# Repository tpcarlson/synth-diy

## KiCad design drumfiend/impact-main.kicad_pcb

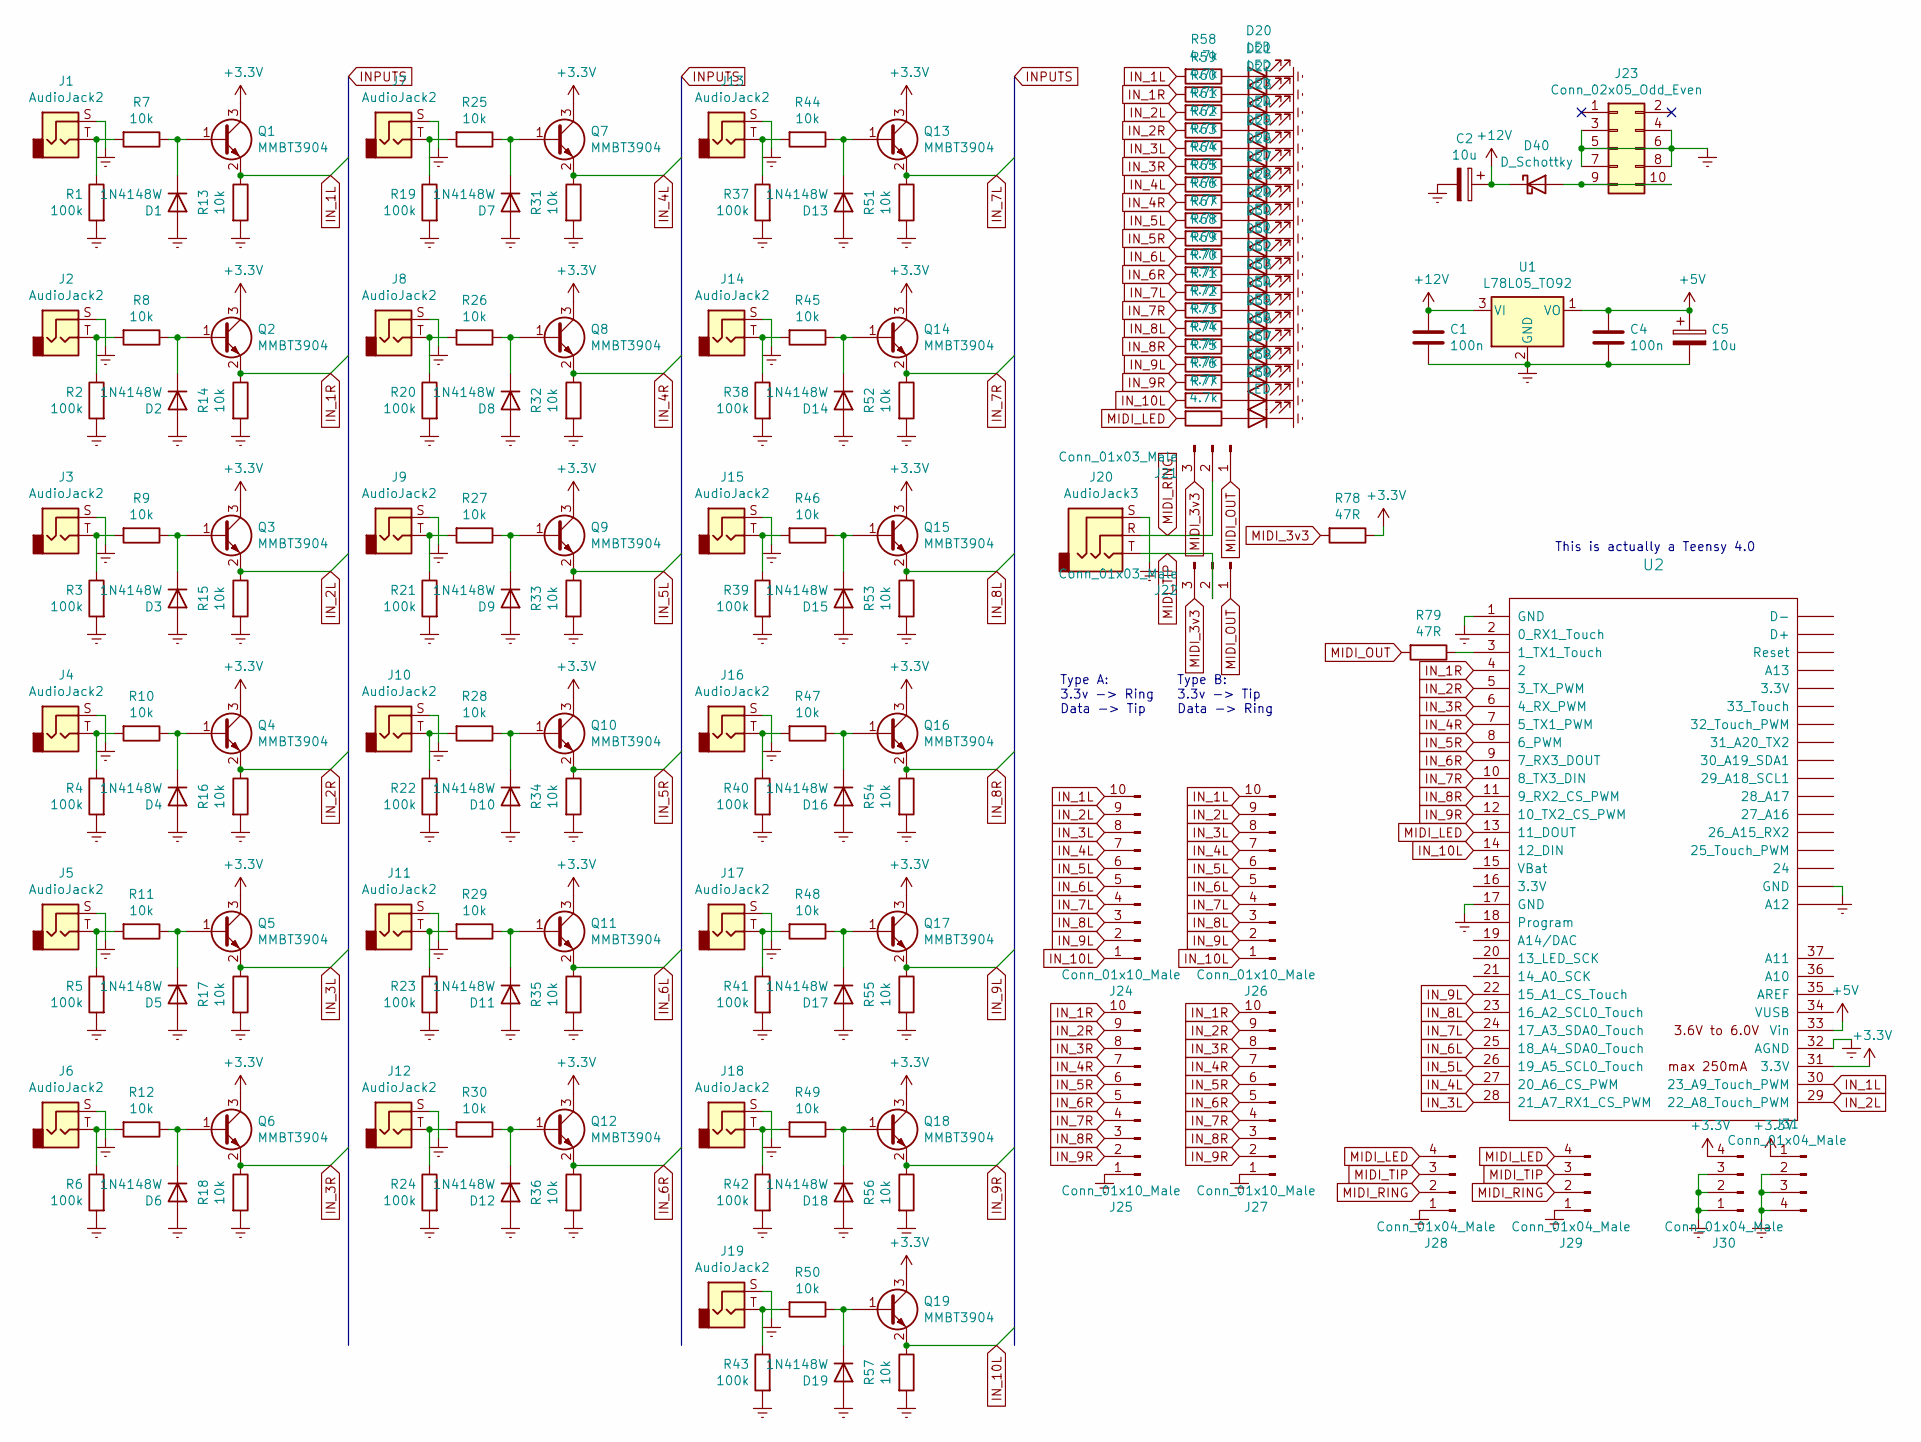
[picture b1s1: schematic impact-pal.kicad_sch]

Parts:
C1, C4: 100n; C_Disc_D5.0mm_W2.5mm_P2.50mm
C2, C5: 10u; CP_Radial_D5.0mm_P2.50mm
D1, D2, D3, D4, D5, D6, D7, D8, D9, D10, D11, D12, D13, D14, D15, D16, D17, D18, D19: 1N4148W; D_SOD-123
D20, D21, D22, D23, D24, D25, D26, D27, D28, D29, D30, D31, D32, D33, D34, D35, D36, D37, D38, D39: LED; LED_D3.0mm
D40: D_Schottky; D_A-405_P7.62mm_Horizontal
J1, J2, J3, J4, J5, J6, J7, J8, J9, J10, J11, J12, J13, J14, J15, J16, J17, J18, J19: AudioJack2; Jack_3.5mm_QingPu_WQP-PJ398SM_Vertical_CircularHoles
J20: AudioJack3; Jack_3.5mm_QingPu_WQP-PJ398SM_Vertical_CircularHoles
J21, J22: Conn_01x03_Male; PinHeader_1x03_P2.54mm_Vertical
J23: Conn_02x05_Odd_Even; IDC-Header_2x05_P2.54mm_Vertical
J24, J25, J26, J27: Conn_01x10_Male; PinHeader_1x10_P2.54mm_Vertical
J28, J29, J30, J31: Conn_01x04_Male; PinHeader_1x04_P2.54mm_Vertical
Q1, Q2, Q3, Q4, Q5, Q6, Q7, Q8, Q9, Q10, Q11, Q12, Q13, Q14, Q15, Q16, Q17, Q18, Q19: MMBT3904; SOT-23
R1, R2, R3, R4, R5, R6, R19, R20, R21, R22, R23, R24, R37, R38, R39, R40, R41, R42, R43: 100k; R_0805_2012Metric
R7, R8, R9, R10, R11, R12, R13, R14, R15, R16, R17, R18, R25, R26, R27, R28, R29, R30, R31, R32, R33, R34, R35, R36, R44, R45, R46, R47, R48, R49, R50, R51, R52, R53, R54, R55, R56, R57: 10k; R_0805_2012Metric
R58, R59, R60, R61, R62, R63, R64, R65, R66, R67, R68, R69, R70, R71, R72, R73, R74, R75, R76, R77: 4.7k; R_0805_2012Metric
R78, R79: 47R; R_Axial_DIN0207_L6.3mm_D2.5mm_P7.62mm_Horizontal
U1: L78L05_TO92; TO-92_Inline_Wide
U2: (no value)

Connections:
+3V3: J30.4, J31.1, Q1.3 (C), Q2.3 (C), Q3.3 (C), Q4.3 (C), Q5.3 (C), Q6.3 (C), Q7.3 (C), Q8.3 (C), Q9.3 (C), Q10.3 (C), Q11.3 (C), Q12.3 (C), Q13.3 (C), Q14.3 (C), Q15.3 (C), Q16.3 (C), Q17.3 (C), Q18.3 (C), Q19.3 (C), R78.1, U2.31 (3.3V)
Earth: C1.2, C2.2, C4.2, C5.2, D1.2 (A), D2.2 (A), D3.2 (A), D4.2 (A), D5.2 (A), D6.2 (A), D7.2 (A), D8.2 (A), D9.2 (A), D10.2 (A), D11.2 (A), D12.2 (A), D13.2 (A), D14.2 (A), D15.2 (A), D16.2 (A), D17.2 (A), D18.2 (A), D19.2 (A), D20.1 (K), D21.1 (K), D22.1 (K), D23.1 (K), D24.1 (K), D25.1 (K), D26.1 (K), D27.1 (K), D28.1 (K), D29.1 (K), D30.1 (K), D31.1 (K), D32.1 (K), D33.1 (K), D34.1 (K), D35.1 (K), D36.1 (K), D37.1 (K), D38.1 (K), D39.1 (K), J1.S, J2.S, J3.S, J4.S, J5.S, J6.S, J7.S, J8.S, J9.S, J10.S, J11.S, J12.S, J13.S, J14.S, J15.S, J16.S, J17.S, J18.S, J19.S, J20.S, J23.3, J23.4, J23.5, J23.6, J23.7, J23.8, J25.1, J27.1, J28.1, J29.1, J30.1, J30.2, J30.3, J31.2, J31.3, J31.4, R1.2, R2.2, R3.2, R4.2, R5.2, R6.2, R13.2, R14.2, R15.2, R16.2, R17.2, R18.2, R19.2, R20.2, R21.2, R22.2, R23.2, R24.2, R31.2, R32.2, R33.2, R34.2, R35.2, R36.2, R37.2, R38.2, R39.2, R40.2, R41.2, R42.2, R43.2, R51.2, R52.2, R53.2, R54.2, R55.2, R56.2, R57.2, U1.2 (GND), U2.1 (GND), U2.17 (GND), U2.32 (AGND), U2.~ (24)
IN_1L: J24.10, J26.10, Q1.2 (E), R13.1, R58.2, U2.30 (23_A9_Touch_PWM)
IN_1R: J25.10, J27.10, Q2.2 (E), R14.1, R59.2, U2.4 (2)
IN_2L: J24.9, J26.9, Q3.2 (E), R15.1, R60.2, U2.29 (22_A8_Touch_PWM)
IN_2R: J25.9, J27.9, Q4.2 (E), R16.1, R61.2, U2.5 (3_TX_PWM)
IN_3L: J24.8, J26.8, Q5.2 (E), R17.1, R62.2, U2.28 (21_A7_RX1_CS_PWM)
IN_3R: J25.8, J27.8, Q6.2 (E), R18.1, R63.2, U2.6 (4_RX_PWM)
IN_4L: J24.7, J26.7, Q7.2 (E), R31.1, R64.2, U2.27 (20_A6_CS_PWM)
IN_4R: J25.7, J27.7, Q8.2 (E), R32.1, R65.2, U2.7 (5_TX1_PWM)
IN_5L: J24.6, J26.6, Q9.2 (E), R33.1, R66.2, U2.26 (19_A5_SCL0_Touch)
IN_5R: J25.6, J27.6, Q10.2 (E), R34.1, R67.2, U2.8 (6_PWM)
IN_6L: J24.5, J26.5, Q11.2 (E), R35.1, R68.2, U2.25 (18_A4_SDA0_Touch)
IN_6R: J25.5, J27.5, Q12.2 (E), R36.1, R69.2, U2.9 (7_RX3_DOUT)
IN_7L: J24.4, J26.4, Q13.2 (E), R51.1, R70.2, U2.24 (17_A3_SDA0_Touch)
IN_7R: J25.4, J27.4, Q14.2 (E), R52.1, R71.2, U2.10 (8_TX3_DIN)
IN_8L: J24.3, J26.3, Q15.2 (E), R53.1, R72.2, U2.23 (16_A2_SCL0_Touch)
IN_8R: J25.3, J27.3, Q16.2 (E), R54.1, R73.2, U2.11 (9_RX2_CS_PWM)
IN_9L: J24.2, J26.2, Q17.2 (E), R55.1, R74.2, U2.22 (15_A1_CS_Touch)
IN_9R: J25.2, J27.2, Q18.2 (E), R56.1, R75.2, U2.12 (10_TX2_CS_PWM)
IN_10L: J24.1, J26.1, Q19.2 (E), R57.1, R76.2, U2.14 (12_DIN)
MIDI_LED: J28.4, J29.4, R77.2, U2.13 (11_DOUT)
MIDI_RING: J20.R, J21.2, J28.2, J29.2
MIDI_TIP: J20.T, J22.2, J28.3, J29.3
unnamed: C1.1, C2.1, D40.1 (K), U1.3 (VI)
unnamed: C4.1, C5.1, U1.1 (VO), U2.33 (Vin)
unnamed: D1.1 (K), Q1.1 (B), R7.1
unnamed: D2.1 (K), Q2.1 (B), R8.1
unnamed: D3.1 (K), Q3.1 (B), R9.1
unnamed: D4.1 (K), Q4.1 (B), R10.1
unnamed: D5.1 (K), Q5.1 (B), R11.1
unnamed: D6.1 (K), Q6.1 (B), R12.1
unnamed: D7.1 (K), Q7.1 (B), R25.1
unnamed: D8.1 (K), Q8.1 (B), R26.1
unnamed: D9.1 (K), Q9.1 (B), R27.1
unnamed: D10.1 (K), Q10.1 (B), R28.1
unnamed: D11.1 (K), Q11.1 (B), R29.1
unnamed: D12.1 (K), Q12.1 (B), R30.1
unnamed: D13.1 (K), Q13.1 (B), R44.1
unnamed: D14.1 (K), Q14.1 (B), R45.1
unnamed: D15.1 (K), Q15.1 (B), R46.1
unnamed: D16.1 (K), Q16.1 (B), R47.1
unnamed: D17.1 (K), Q17.1 (B), R48.1
unnamed: D18.1 (K), Q18.1 (B), R49.1
unnamed: D19.1 (K), Q19.1 (B), R50.1
unnamed: D20.2 (A), R58.1
unnamed: D21.2 (A), R59.1
unnamed: D22.2 (A), R60.1
unnamed: D23.2 (A), R61.1
unnamed: D24.2 (A), R62.1
unnamed: D25.2 (A), R63.1
unnamed: D26.2 (A), R64.1
unnamed: D27.2 (A), R65.1
unnamed: D28.2 (A), R66.1
unnamed: D29.2 (A), R67.1
unnamed: D30.2 (A), R68.1
unnamed: D31.2 (A), R69.1
unnamed: D32.2 (A), R70.1
unnamed: D33.2 (A), R71.1
unnamed: D34.2 (A), R72.1
unnamed: D35.2 (A), R73.1
unnamed: D36.2 (A), R74.1
unnamed: D37.2 (A), R75.1
unnamed: D38.2 (A), R76.1
unnamed: D39.2 (A), R77.1
unnamed: D40.2 (A), J23.9, J23.10
unnamed: J1.T, R1.1, R7.2
unnamed: J2.T, R2.1, R8.2
unnamed: J3.T, R3.1, R9.2
unnamed: J4.T, R4.1, R10.2
unnamed: J5.T, R5.1, R11.2
unnamed: J6.T, R6.1, R12.2
unnamed: J7.T, R19.1, R25.2
unnamed: J8.T, R20.1, R26.2
unnamed: J9.T, R21.1, R27.2
unnamed: J10.T, R22.1, R28.2
unnamed: J11.T, R23.1, R29.2
unnamed: J12.T, R24.1, R30.2
unnamed: J13.T, R37.1, R44.2
unnamed: J14.T, R38.1, R45.2
unnamed: J15.T, R39.1, R46.2
unnamed: J16.T, R40.1, R47.2
unnamed: J17.T, R41.1, R48.2
unnamed: J18.T, R42.1, R49.2
unnamed: J19.T, R43.1, R50.2
unnamed: J21.1, J22.1, R79.2
unnamed: J21.3, J22.3, R78.2
unnamed: R79.1, U2.3 (1_TX1_Touch)

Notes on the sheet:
Type B: 3.3v -> Tip Data -> Ring
Type A: 3.3v -> Ring Data -> Tip
This is actually a Teensy 4.0

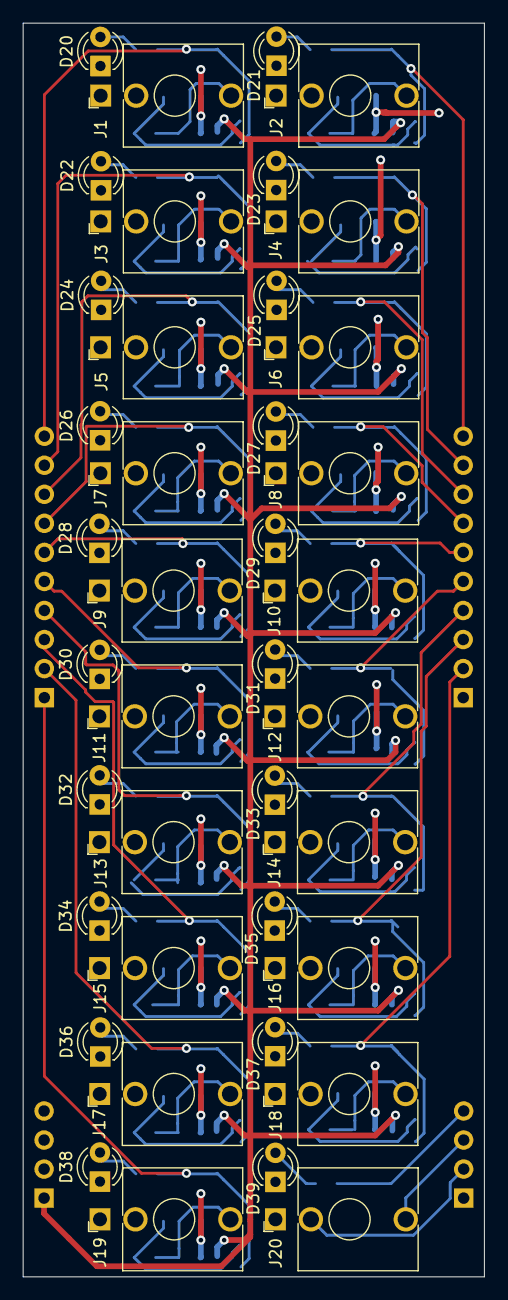
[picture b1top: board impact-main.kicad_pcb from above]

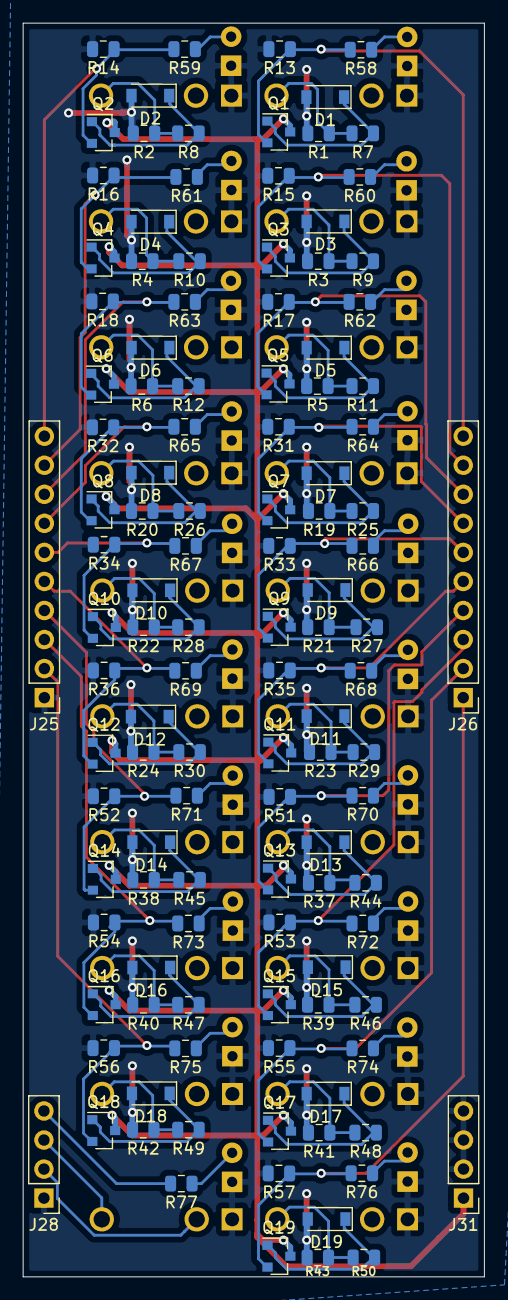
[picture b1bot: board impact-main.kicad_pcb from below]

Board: 2 copper layers, 40.3 x 109.6 mm, 159 parts (119 on the bottom side), 82 nets.

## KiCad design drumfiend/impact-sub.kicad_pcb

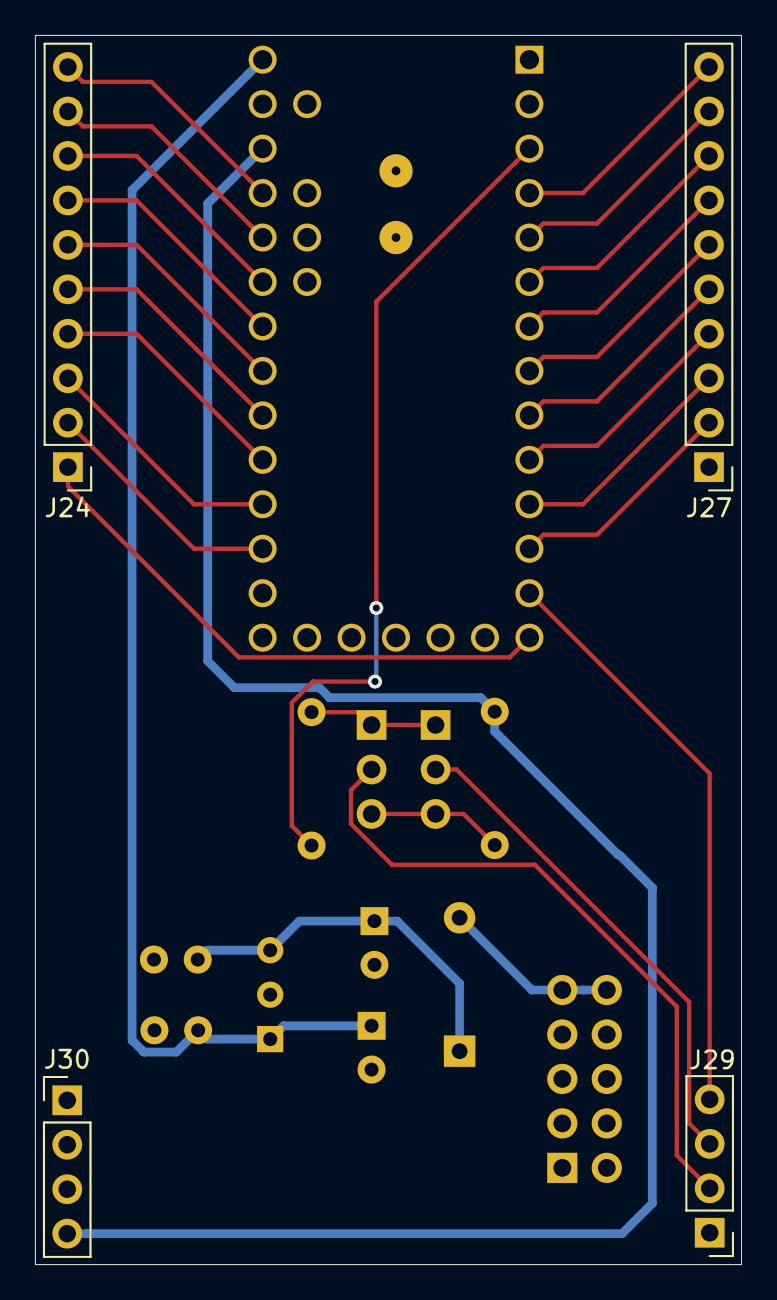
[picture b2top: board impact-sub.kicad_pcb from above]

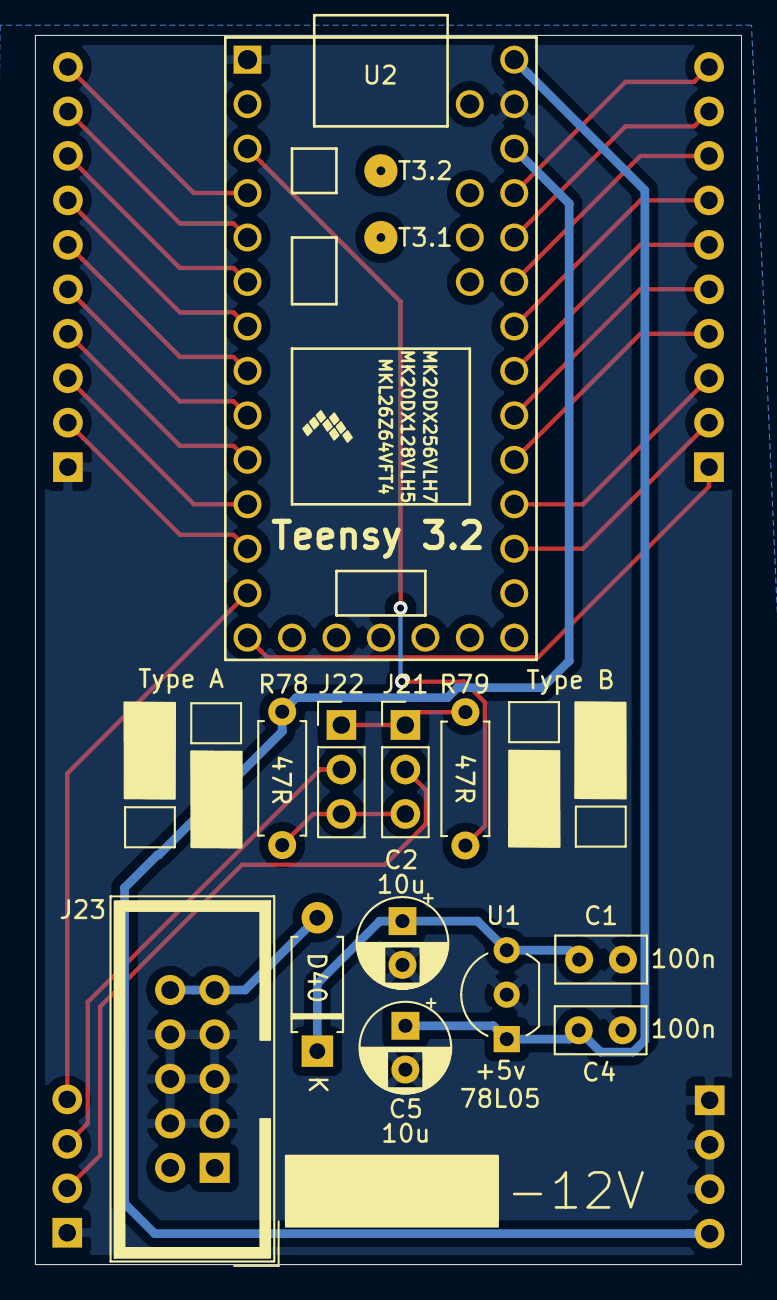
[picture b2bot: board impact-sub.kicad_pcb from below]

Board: 2 copper layers, 40.3 x 70.2 mm, 16 parts (12 on the bottom side), 30 nets.

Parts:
C1, C4: 100n; C_Disc_D5.0mm_W2.5mm_P2.50mm
C2, C5: 10u; CP_Radial_D5.0mm_P2.50mm
D40: D_Schottky; D_A-405_P7.62mm_Horizontal
J21, J22: Conn_01x03_Male; PinHeader_1x03_P2.54mm_Vertical
J23: Conn_02x05_Odd_Even; IDC-Header_2x05_P2.54mm_Vertical
J24, J27: Conn_01x10_Male; PinHeader_1x10_P2.54mm_Vertical
J29, J30: Conn_01x04_Male; PinHeader_1x04_P2.54mm_Vertical
R78, R79: 47R; R_Axial_DIN0207_L6.3mm_D2.5mm_P7.62mm_Horizontal
U1: L78L05_TO92; TO-92_Inline_Wide
U2: Teensy3.2; Teensy30_31_32_LC

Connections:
+3V3: J30.4, R78.1, U2.31
+5V: C4.1, C5.1, U1.1, U2.33
+12V: C1.1, C2.1, D40.1, U1.3
Earth: C1.2, C2.2, C4.2, C5.2, J23.3, J23.4, J23.5, J23.6, J23.7, J23.8, J27.1, J29.1, J30.1, J30.2, J30.3, U1.2, U2.1, U2.17, U2.32
IN_1L: J24.10, U2.30
IN_1R: J27.10, U2.4
IN_2L: J24.9, U2.29
IN_2R: J27.9, U2.5
IN_3L: J24.8, U2.28
IN_3R: J27.8, U2.6
IN_4L: J24.7, U2.27
IN_4R: J27.7, U2.7
IN_5L: J24.6, U2.26
IN_5R: J27.6, U2.8
IN_6L: J24.5, U2.25
IN_6R: J27.5, U2.9
IN_7L: J24.4, U2.24
IN_7R: J27.4, U2.10
IN_8L: J24.3, U2.23
IN_8R: J27.3, U2.11
IN_9L: J24.2, U2.22
IN_9R: J27.2, U2.12
IN_10L: J24.1, U2.14
MIDI_3v3: J21.3, J22.3, R78.2
MIDI_LED: J29.4, U2.13
MIDI_OUT: J21.1, J22.1, R79.2
MIDI_RING: J21.2, J29.2
MIDI_TIP: J22.2, J29.3
unnamed: D40.2, J23.9, J23.10
unnamed: R79.1, U2.3

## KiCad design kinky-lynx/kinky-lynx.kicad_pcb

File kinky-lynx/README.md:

# Kinky Lynx

##### What is this?

A mashup of Mutable Instruments' [Kinks](https://mutable-instruments.net/modules/kinks/) and [Links](https://mutable-instruments.net/modules/links/) all on one board.

##### How much power does it use?

(TBC) As measured by the joranalogue Test 3, around x mA on +12v and y mA on -12v at peak. The 5v rail is unused.

##### Where does the design come from?

This is just a copy of the Kinks and Links schematics jammed together on one PCB, with a couple of very small component changes to allow for easier assembly.

##### Are there any rare/weird parts used?

All fairly common parts. Some of the capacitors are quite small (0402 sized) which will make hand soldering a challenge, I had my boards assembled by the PCB fab. I used two pin bicolour LEDs, but you can substitute them for a normal 3mm LED.

##### Are there any problems with the design?

The topmost row (One in three out) seems to pull the LED to a negative voltage when nothing is plugged in, but other than everything works well!

##### Do you have a BOM/Mouser cart/Tayda links?

Sorry, no. Things go out of stock so frequently it'd be a lot of work to keep these up to date. Everything in this project is easy to source though, so you should not have any trouble.

##### Can I buy PCBs or a kit?

Send me an email (twigathy+synth@gmail.com)...

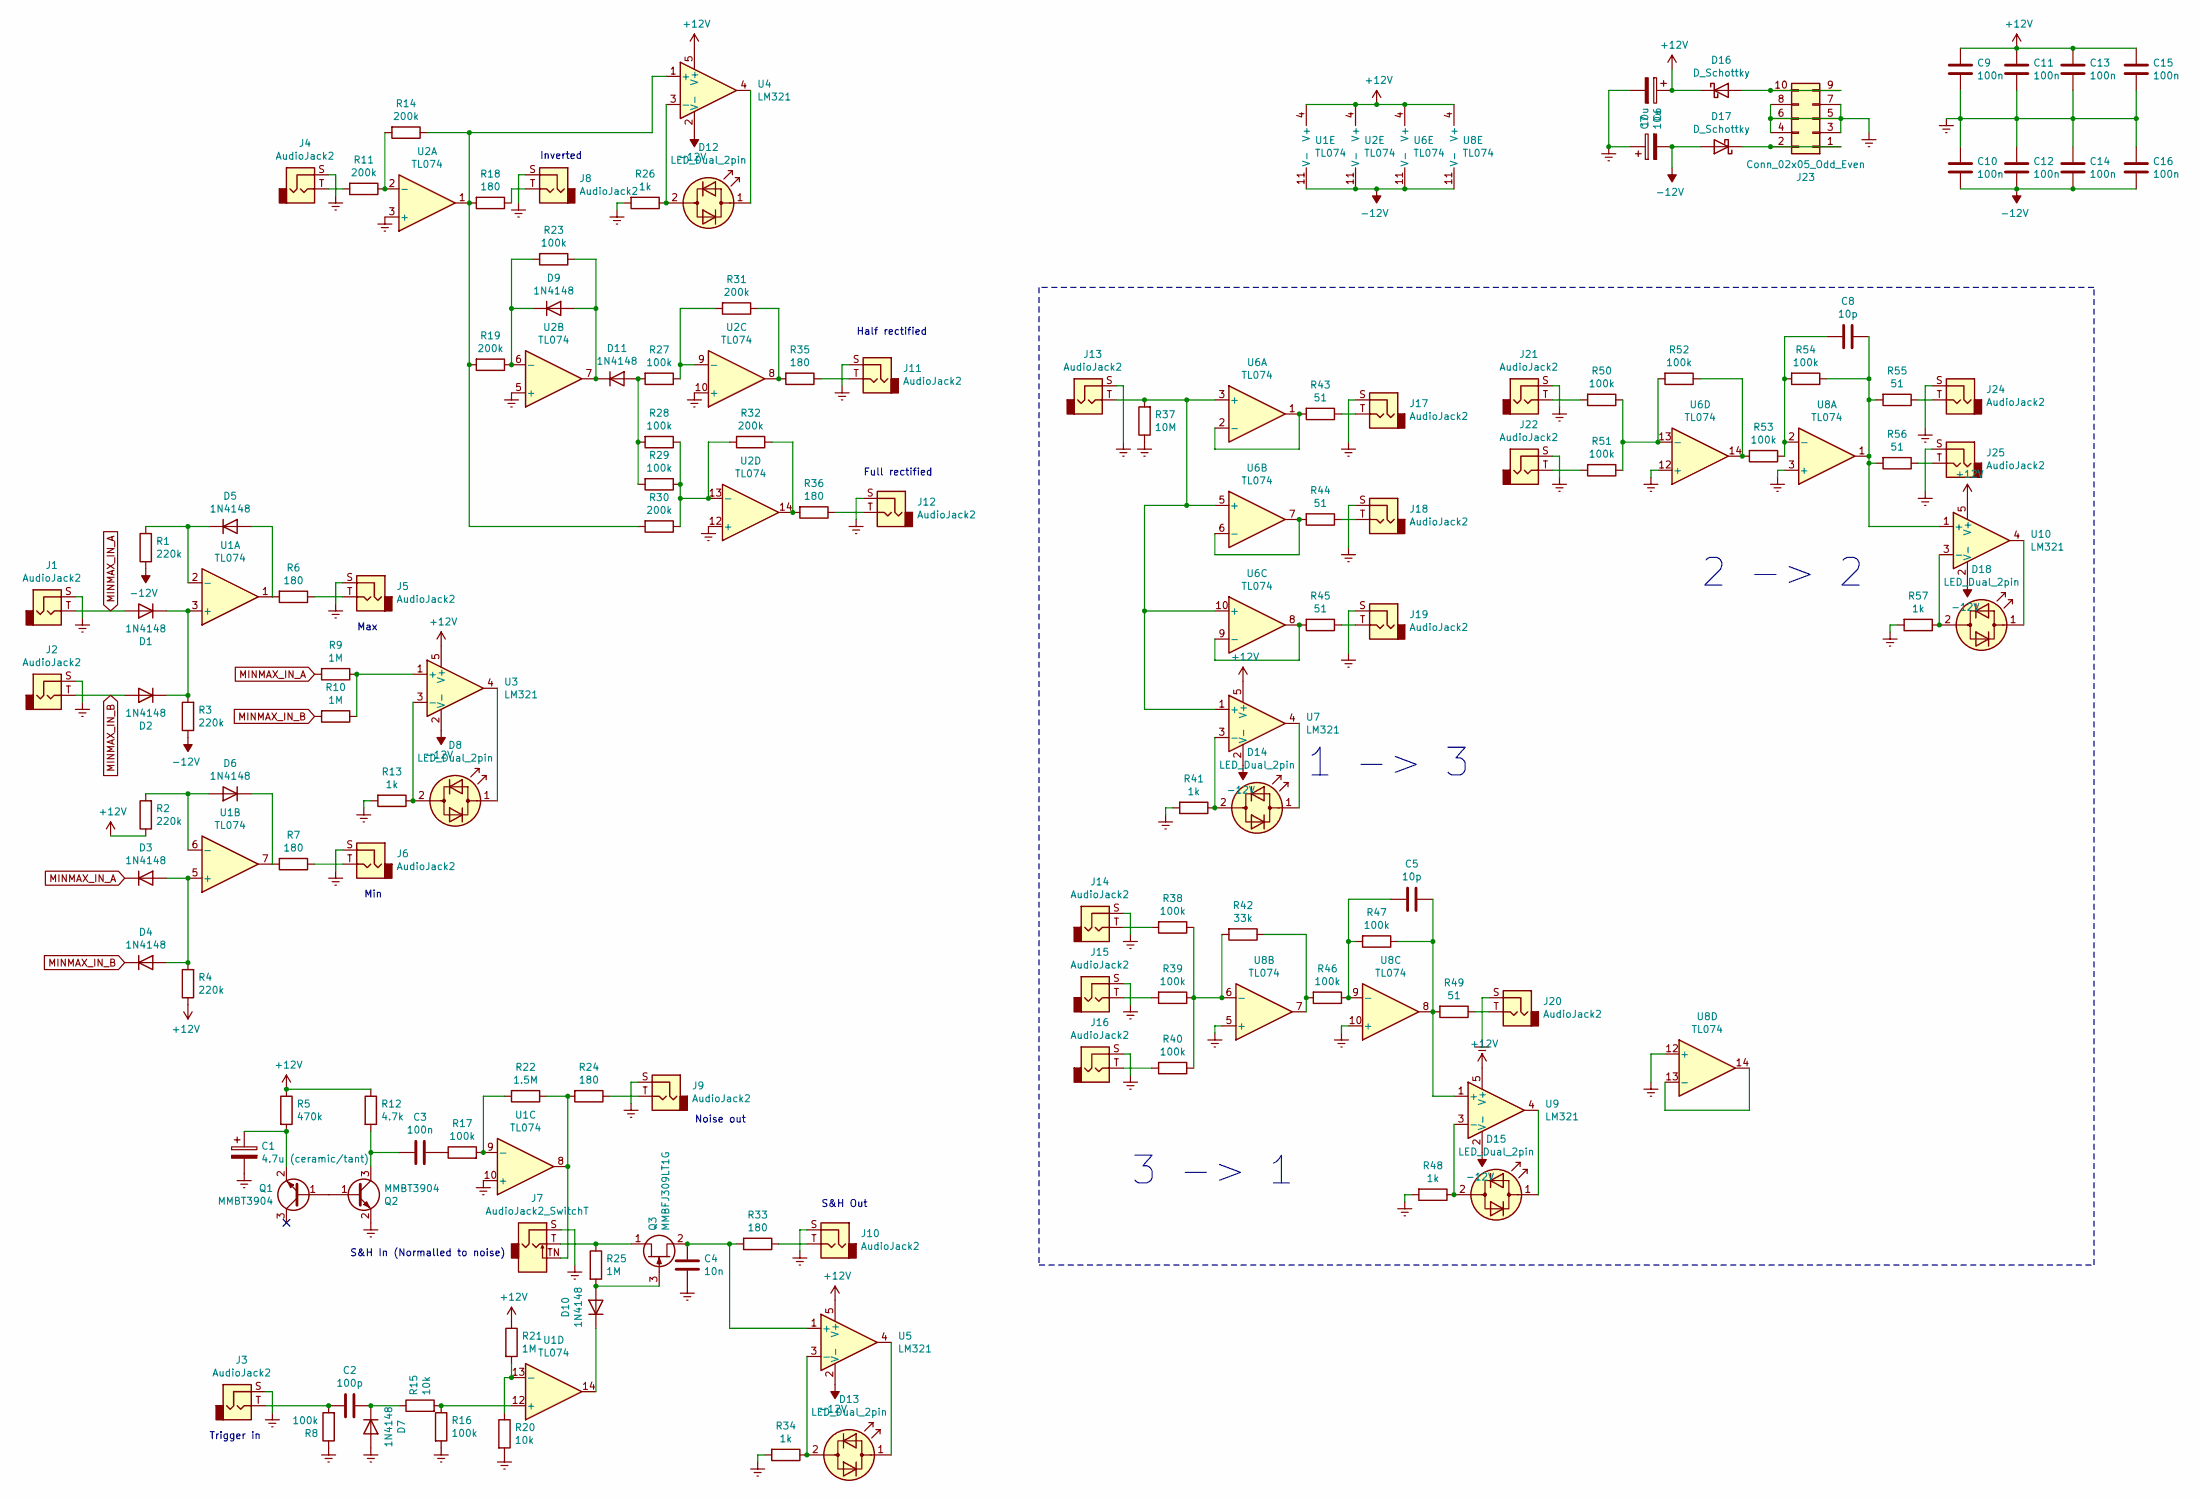
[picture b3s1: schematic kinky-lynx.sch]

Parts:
C1: 4.7u (ceramic/tant); C_0603_1608Metric
C2: 100p; C_0402_1005Metric
C3, C9, C10, C11, C12, C13, C14, C15, C16: 100n; C_0402_1005Metric
C4: 10n; C_0402_1005Metric
C5, C8: 10p; C_0402_1005Metric
C6, C7: 10u; CP_Radial_D5.0mm_P2.50mm
D1, D2, D3, D4, D5, D6, D7, D9, D10, D11: 1N4148; D_SOD-123
D8, D12, D13, D14, D15, D18: LED_Dual_2pin; LED_D3.0mm
D16, D17: D_Schottky; D_A-405_P7.62mm_Horizontal
J1, J2, J3, J4, J5, J6, J8, J9, J10, J11, J12, J13, J14, J15, J16, J17, J18, J19, J20, J21, J22, J24, J25: AudioJack2; Jack_3.5mm_QingPu_WQP-PJ398SM_Vertical_CircularHoles
J7: AudioJack2_SwitchT; Jack_3.5mm_QingPu_WQP-PJ398SM_Vertical_CircularHoles
J23: Conn_02x05_Odd_Even; IDC-Header_2x05_P2.54mm_Vertical
Q1, Q2: MMBT3904; SOT-23
Q3: MMBFJ309LT1G; SOT-23
R1, R2, R3, R4: 220k; R_0603_1608Metric
R5: 470k; R_0603_1608Metric
R6, R7, R18, R24, R33, R35, R36: 180; R_0603_1608Metric
R8, R16, R17, R23, R27, R28, R29, R38, R39, R40, R46, R47, R50, R51, R52, R53, R54: 100k; R_0603_1608Metric
R9, R10, R21, R25: 1M; R_0603_1608Metric
R11, R14, R19, R30, R31, R32: 200k; R_0603_1608Metric
R12: 4.7k; R_0603_1608Metric
R13, R26, R34, R41, R48, R57: 1k; R_0603_1608Metric
R15, R20: 10k; R_0603_1608Metric
R22: 1.5M; R_0603_1608Metric
R37: 10M; R_0603_1608Metric
R42: 33k; R_0603_1608Metric
R43, R44, R45, R49, R55, R56: 51; R_0603_1608Metric
U1, U2, U6, U8: TL074; SOIC-14_3.9x8.7mm_P1.27mm
U3, U4, U5, U7, U9, U10: LM321; SOT-23-5

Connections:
+12V: C6.1, C9.1, C11.1, C13.1, C15.1, D16.1 (K), R2.1, R4.1, R5.1, R12.1, R21.1, U1.4 (V+), U2.4 (V+), U3.5 (V+), U4.5 (V+), U5.5 (V+), U6.4 (V+), U7.5 (V+), U8.4 (V+), U9.5 (V+), U10.5 (V+)
-12V: C7.2, C10.2, C12.2, C14.2, C16.2, D17.2 (A), R1.1, R3.1, U1.11 (V-), U2.11 (V-), U3.2 (V-), U4.2 (V-), U5.2 (V-), U6.11 (V-), U7.2 (V-), U8.11 (V-), U9.2 (V-), U10.2 (V-)
Earth: C1.2, C4.2, C6.2, C7.1, C9.2, C10.1, C11.2, C12.1, C13.2, C14.1, C15.2, C16.1, D7.2 (A), J1.S, J2.S, J3.S, J4.S, J5.S, J6.S, J7.S, J8.S, J9.S, J10.S, J11.S, J12.S, J13.S, J14.S, J15.S, J16.S, J17.S, J18.S, J19.S, J20.S, J21.S, J22.S, J23.3, J23.4, J23.5, J23.6, J23.7, J23.8, J24.S, J25.S, Q2.2 (E), R8.1, R13.2, R16.2, R20.2, R26.2, R34.2, R37.1, R41.2, R48.2, R57.2, U1.10 (+), U2.3 (+), U2.5 (+), U2.10 (+), U2.12 (+), U6.12 (+), U8.3 (+), U8.5 (+), U8.10 (+), U8.12 (+)
MINMAX_IN_A: D1.2 (A), D3.1 (K), J1.T, R9.2
MINMAX_IN_B: D2.2 (A), D4.1 (K), J2.T, R10.2
unnamed: C1.1, Q1.2 (E), R5.2
unnamed: C2.1, D7.1 (K), R15.1
unnamed: C2.2, J3.T, R8.2
unnamed: C3.1, R17.1
unnamed: C3.2, Q2.3 (C), R12.2
unnamed: C4.1, Q3.2 (S), R33.2, U5.1 (+)
unnamed: C5.1, R47.1, R49.2, U8.8, U9.1 (+)
unnamed: C5.2, R46.1, R47.2, U8.9 (-)
unnamed: C8.1, R54.1, R55.2, R56.2, U8.1, U10.1 (+)
unnamed: C8.2, R53.1, R54.2, U8.2 (-)
unnamed: D1.1 (K), D2.1 (K), R3.2, U1.3 (+)
unnamed: D3.2 (A), D4.2 (A), R4.2, U1.5 (+)
unnamed: D5.1 (K), R1.2, U1.2 (-)
unnamed: D5.2 (A), R6.2, U1.1
unnamed: D6.1 (K), R7.2, U1.7
unnamed: D6.2 (A), R2.2, U1.6 (-)
unnamed: D8.1 (KA), U3.4
unnamed: D8.2 (AK), R13.1, U3.3 (-)
unnamed: D9.1 (K), R19.1, R23.2, U2.6 (-)
unnamed: D10.1 (K), U1.14
unnamed: D10.2 (A), Q3.3 (G), R25.2
unnamed: D9.2 (A), D11.1 (K), R23.1, U2.7
unnamed: D11.2 (A), R27.2, R28.2, R29.2
unnamed: D12.1 (KA), U4.4
unnamed: D12.2 (AK), R26.1, U4.3 (-)
unnamed: D13.1 (KA), U5.4
unnamed: D13.2 (AK), R34.1, U5.3 (-)
unnamed: D14.1 (KA), U7.4
unnamed: D14.2 (AK), R41.1, U7.3 (-)
unnamed: D15.1 (KA), U9.4
unnamed: D15.2 (AK), R48.1, U9.3 (-)
unnamed: D16.2 (A), J23.9, J23.10
unnamed: D17.1 (K), J23.1, J23.2
unnamed: D18.1 (KA), U10.4
unnamed: D18.2 (AK), R57.1, U10.3 (-)
unnamed: J4.T, R11.2
unnamed: J5.T, R6.1
unnamed: J6.T, R7.1
unnamed: J7.T, Q3.1 (D), R25.1
unnamed: J7.TN, R22.1, R24.2, U1.8
unnamed: J8.T, R18.1
unnamed: J9.T, R24.1
unnamed: J10.T, R33.1
unnamed: J11.T, R35.1
unnamed: J12.T, R36.1
unnamed: J13.T, R37.2, U6.3 (+), U6.5 (+), U6.10 (+), U7.1 (+)
unnamed: J14.T, R38.2
unnamed: J15.T, R39.2
unnamed: J16.T, R40.2
unnamed: J17.T, R43.1
unnamed: J18.T, R44.1
unnamed: J19.T, R45.1
unnamed: J20.T, R49.1
unnamed: J21.T, R50.2
unnamed: J22.T, R51.2
unnamed: J24.T, R55.1
unnamed: J25.T, R56.1
unnamed: Q1.1 (B), Q2.1 (B)
unnamed: R9.1, R10.1, U3.1 (+)
unnamed: R11.1, R14.2, U2.2 (-)
unnamed: R14.1, R18.2, R19.2, R30.2, U2.1, U4.1 (+)
unnamed: R15.2, R16.1, U1.12 (+)
unnamed: R17.2, R22.2, U1.9 (-)
unnamed: R20.1, R21.2, U1.13 (-)
unnamed: R27.1, R31.2, U2.9 (-)
unnamed: R28.1, R29.1, R30.1, R32.2, U2.13 (-)
unnamed: R31.1, R35.2, U2.8
unnamed: R32.1, R36.2, U2.14
unnamed: R38.1, R39.1, R40.1, R42.2, U8.6 (-)
unnamed: R42.1, R46.2, U8.7
unnamed: R43.2, U6.1, U6.2 (-)
unnamed: R44.2, U6.6 (-), U6.7
unnamed: R45.2, U6.8, U6.9 (-)
unnamed: R50.1, R51.1, R52.2, U6.13 (-)
unnamed: R52.1, R53.2, U6.14
unnamed: U8.13 (-), U8.14

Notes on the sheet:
1 -> 3
2 -> 2
3 -> 1
Min
Max
Noise out
S&H Out
S&H In (Normalled to noise)
Trigger in
Inverted
Half rectified
Full rectified

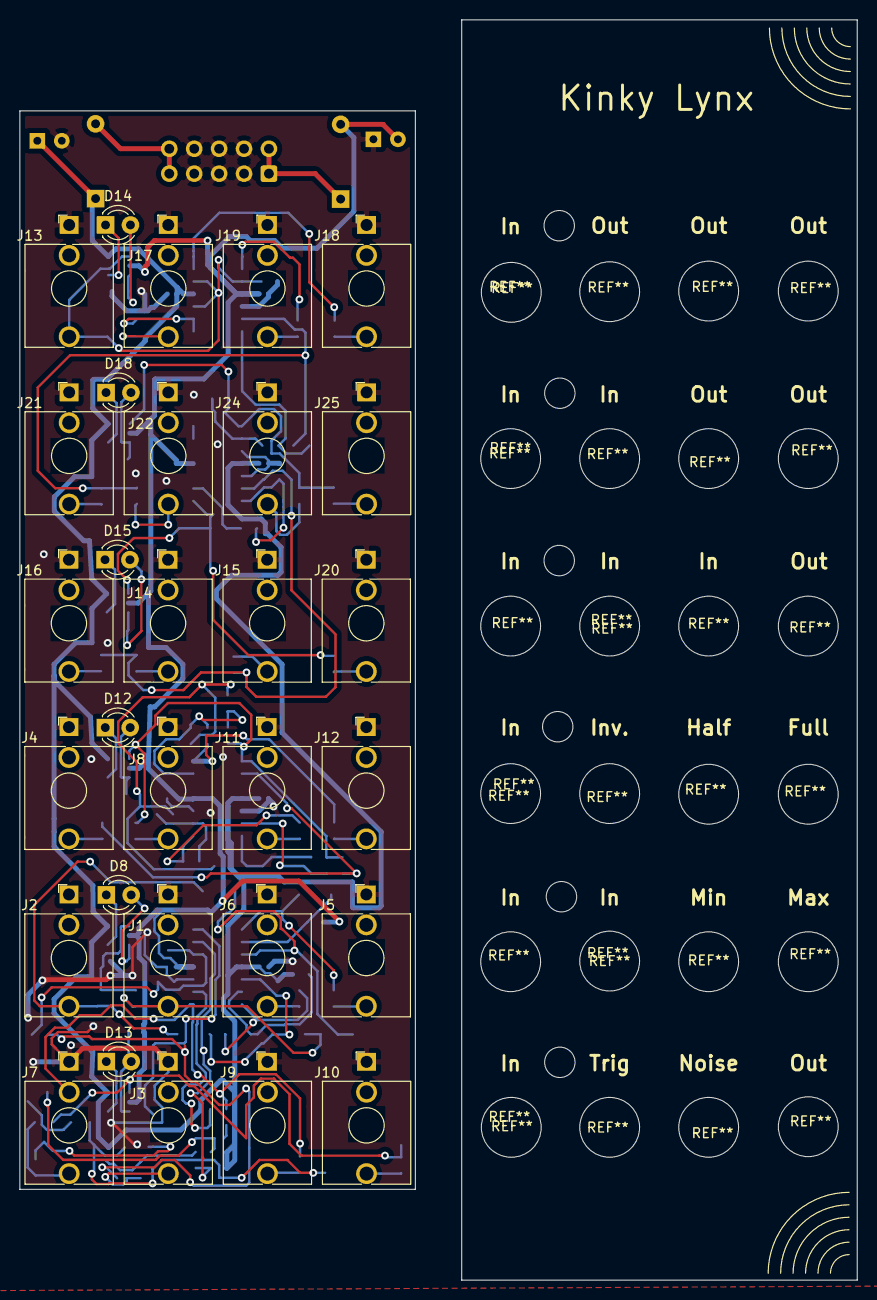
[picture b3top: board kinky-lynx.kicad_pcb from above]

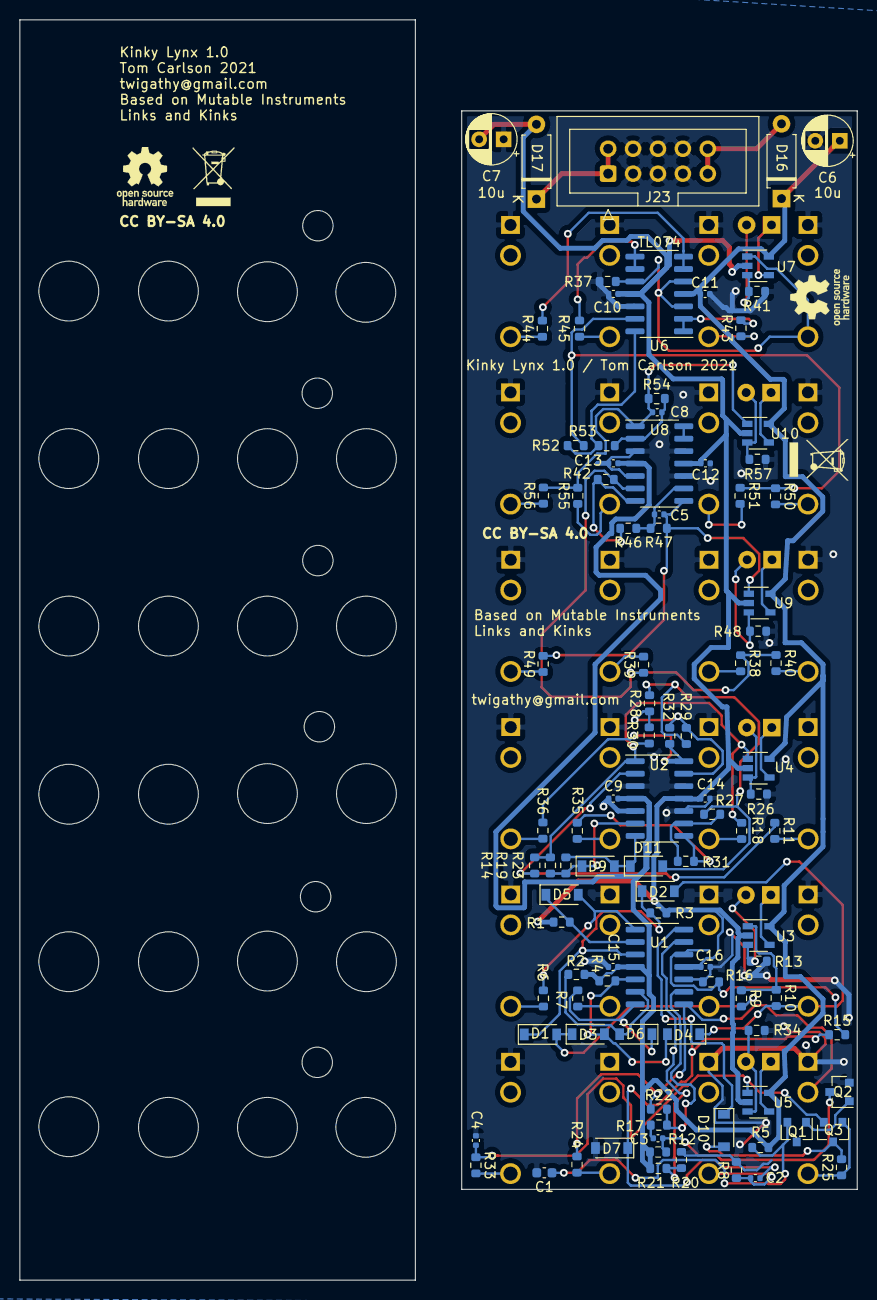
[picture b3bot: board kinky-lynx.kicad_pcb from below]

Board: 2 copper layers, 40.3 x 110.0 mm, 133 parts (103 on the bottom side), 81 nets.

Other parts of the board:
J26, J26#2: WEEE; WEEE-Logo_4.2x6mm_SilkScreen
J27, J27#2: OSHW; OSHW-Logo_5.7x6mm_SilkScreen

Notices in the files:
kinky-lynx/kinky-lynx.kicad_pcb:
CC BY-SA 4.0
lattice/lattice/lattice.kicad_pcb:
CC BY-SA 3.0
